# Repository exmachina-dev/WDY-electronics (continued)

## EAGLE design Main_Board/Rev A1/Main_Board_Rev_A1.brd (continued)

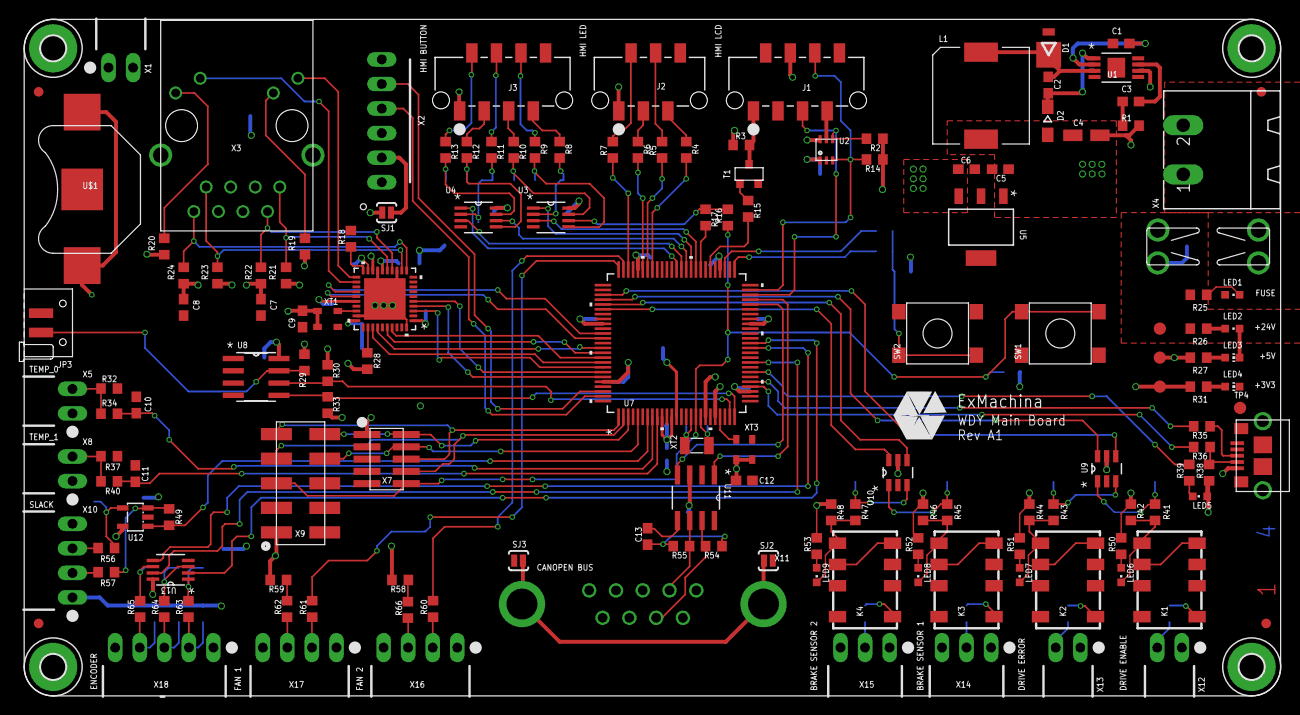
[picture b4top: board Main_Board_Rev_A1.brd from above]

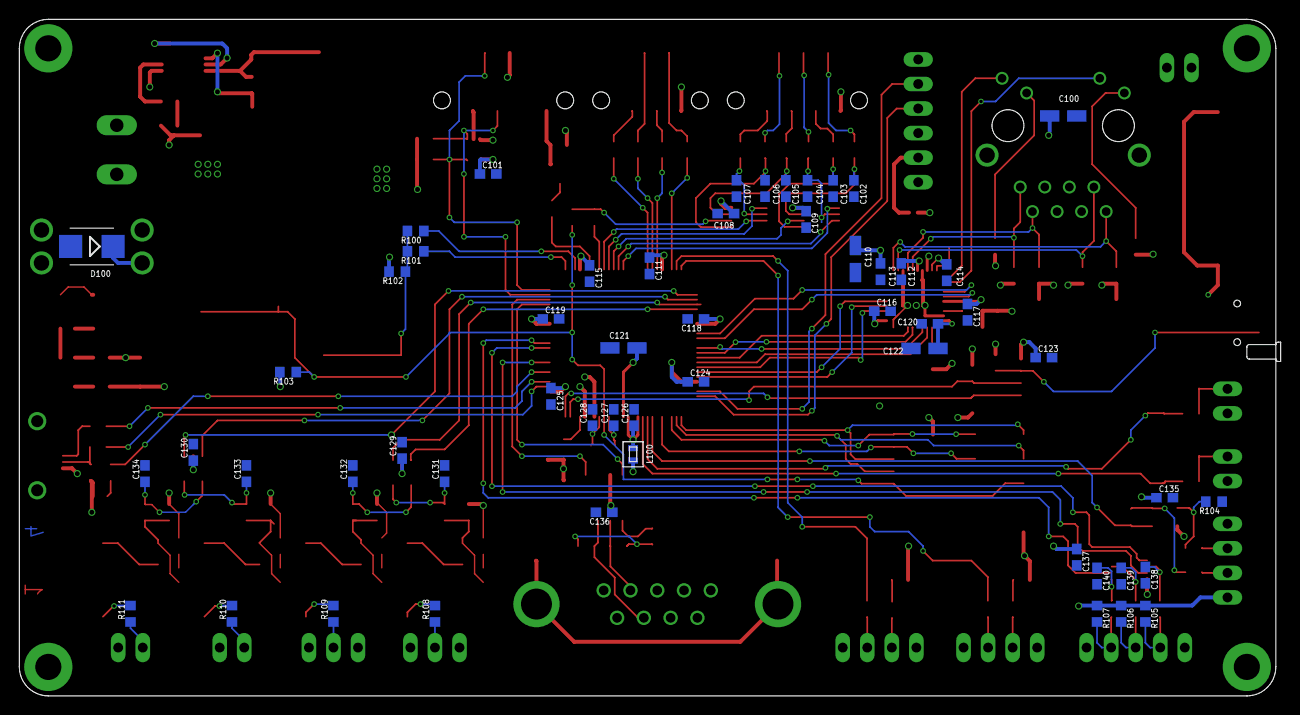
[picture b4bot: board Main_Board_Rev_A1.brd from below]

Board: 4 copper layers, 130.0 x 70.0 mm, 209 parts (55 on the bottom side), 154 nets.

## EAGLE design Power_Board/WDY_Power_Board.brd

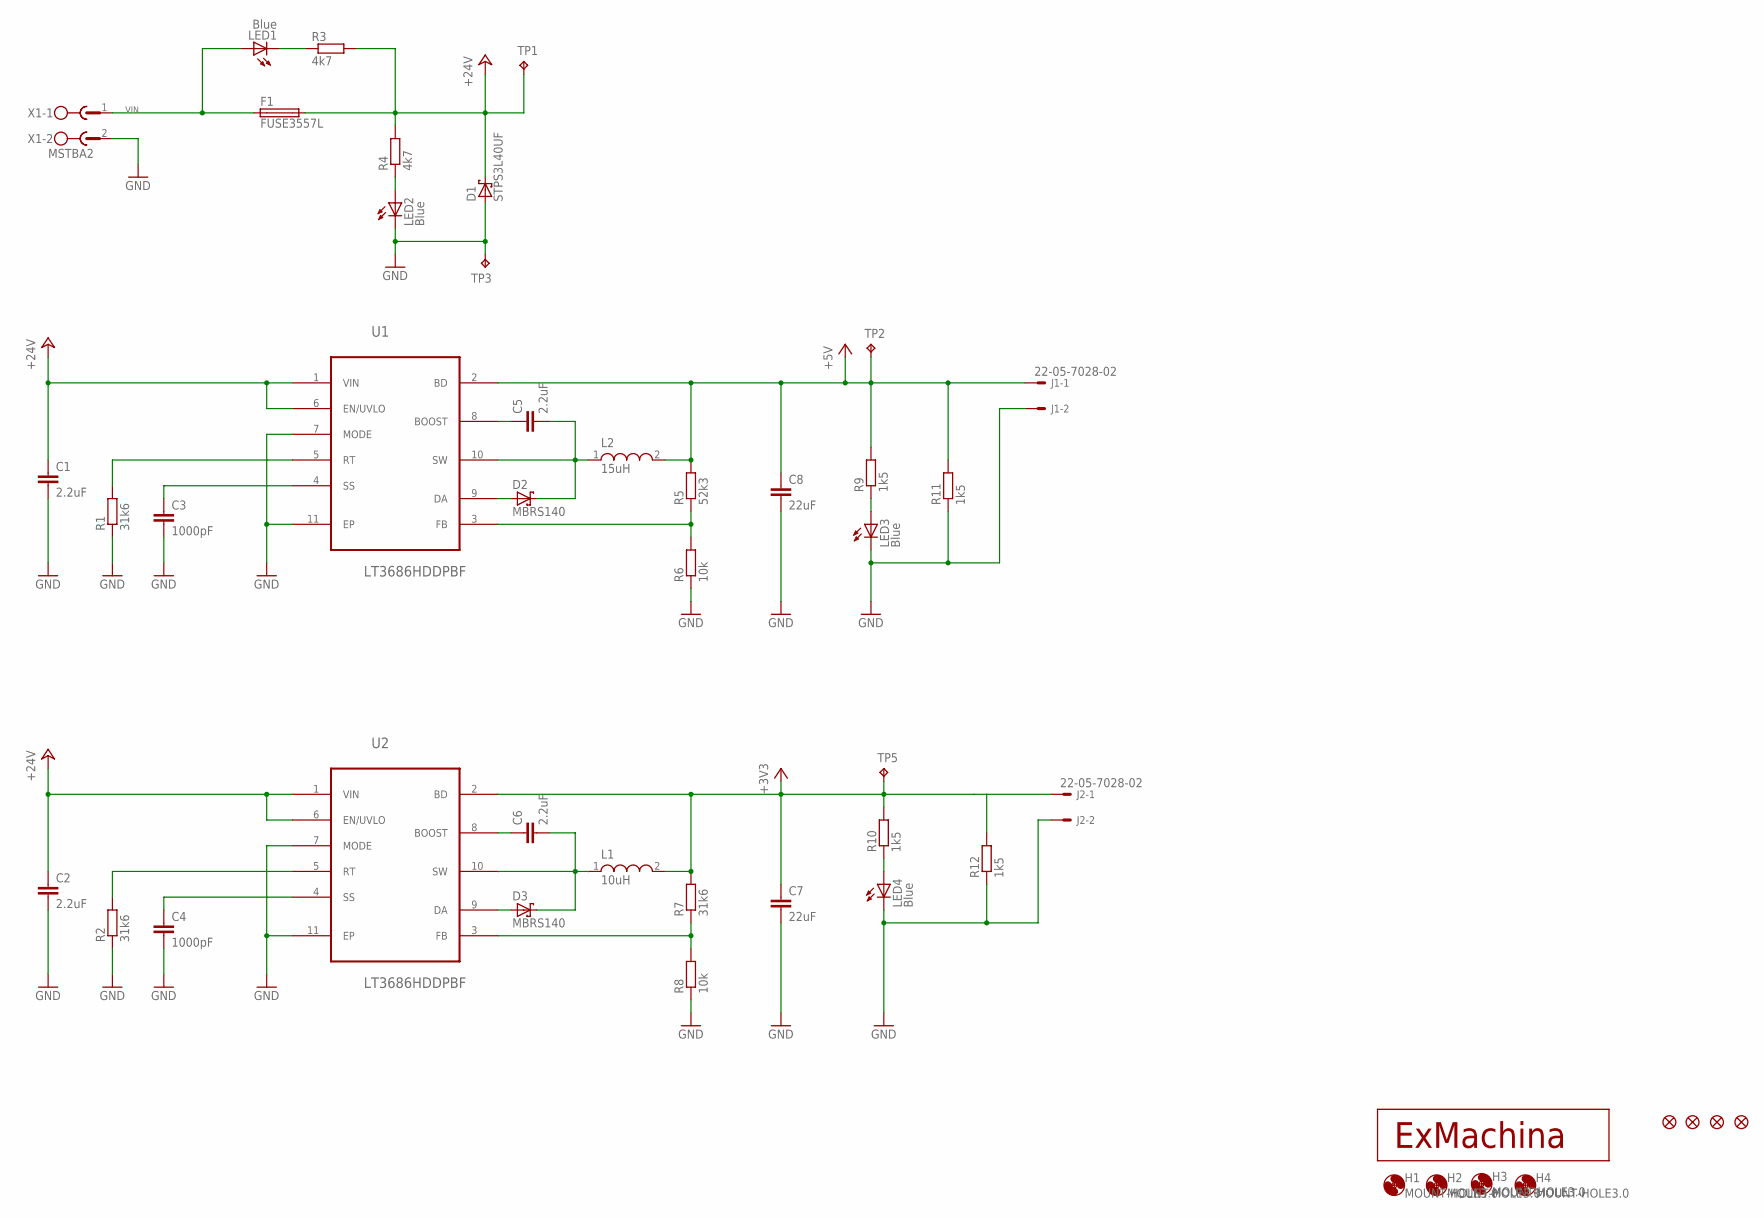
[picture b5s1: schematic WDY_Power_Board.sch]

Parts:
C1, C2, C5, C6: 2.2uF; C0603; MPN GRT188R61H225KE13D
C3, C4: 1000pF; C0603; MPN MC0603B102K500CT
C7, C8: 22uF; C0805; MPN MCMT21N220F250CT
D1: STPS3L40UF; SMB
D2, D3: MBRS140; DO-214AA; MPN MBRS140T3G
F1: FUSE3557L; 3557-LITTLE; MPN 3557
H1, H2, H3, H4: MOUNT-HOLE3.0; 3,0
J1, J2: 22-05-7028-02; 7395-02; MPN 22-05-7028
JP1, JP2, JP3, JP4: FIDUCIAL1X2; FIDUCIAL-1X2
L1: 10uH; WE-PD2_5848/5820; MPN 74477410
L2: 15uH; WE-PD2_5848/5820; MPN 744774115
LED1, LED2: Blue; CHIPLED_0603; MPN OVS-0603
LED3, LED4: Blue; CHIP-LED0603; MPN OVS-0604
R1, R2, R7: 31k6; R0603; MPN MC0063W060311K5
R3, R4: 4k7; R0603; MPN MCMR06X4701FTL
R5: 52k3; R0603; MPN MC0063W0603152K3
R6, R8: 10k; R0603; MPN MCMR06X1002FTL
R9, R10, R11, R12: 1k5; R0603; MPN MC0063W060311K5
TP1, TP2, TP3, TP5: TPB1,27; B1,27
U1, U2: LT3686HDDPBF; DFN300X300X80-11N
U$1: EXMACHINA-LOGO-NAME; EXM-LOGO-BASELINE
X1: MSTBA2

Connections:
+3V3: C7.1, J2.1, L1.2, R7.2, R10.2, R12.2, TP5.TP, U2.2 (BD)
+5V: C8.1, J1.1, L2.2, R5.2, R9.2, R11.2, TP2.TP, U1.2 (BD)
+24V: C1.1, C2.1, D1.C, F1.3 (2), F1.4 (2), R3.2, R4.2, TP1.TP, U1.1 (VIN), U1.6 (EN/UVLO), U2.1 (VIN), U2.6 (EN/UVLO)
GND: C1.2, C2.2, C3.2, C4.2, C7.2, C8.2, D1.A, J1.2, J2.2, LED2.C, LED3.C, LED4.C, R1.1, R2.1, R6.1, R8.1, R11.1, R12.1, TP3.TP, U1.7 (MODE), U1.11 (EP), U2.7 (MODE), U2.11 (EP), X1.2
unnamed: R1.2, U1.5 (RT)
unnamed: R7.1, R8.2, U2.3 (FB)
unnamed: C3.1, U1.4 (SS)
unnamed: R2.2, U2.5 (RT)
unnamed: C4.1, U2.4 (SS)
unnamed: R5.1, R6.2, U1.3 (FB)
unnamed: C6.1, U2.8 (BOOST)
unnamed: C5.1, U1.8 (BOOST)
unnamed: C5.2, D2.C, L2.1, U1.10 (SW)
unnamed: D2.A, U1.9 (DA)
unnamed: C6.2, D3.C, L1.1, U2.10 (SW)
unnamed: D3.A, U2.9 (DA)
unnamed: LED2.A, R4.1
unnamed: LED1.C, R3.1
unnamed: LED4.A, R10.1
unnamed: LED3.A, R9.1
VIN: F1.1, F1.2 (1), LED1.A, X1.1

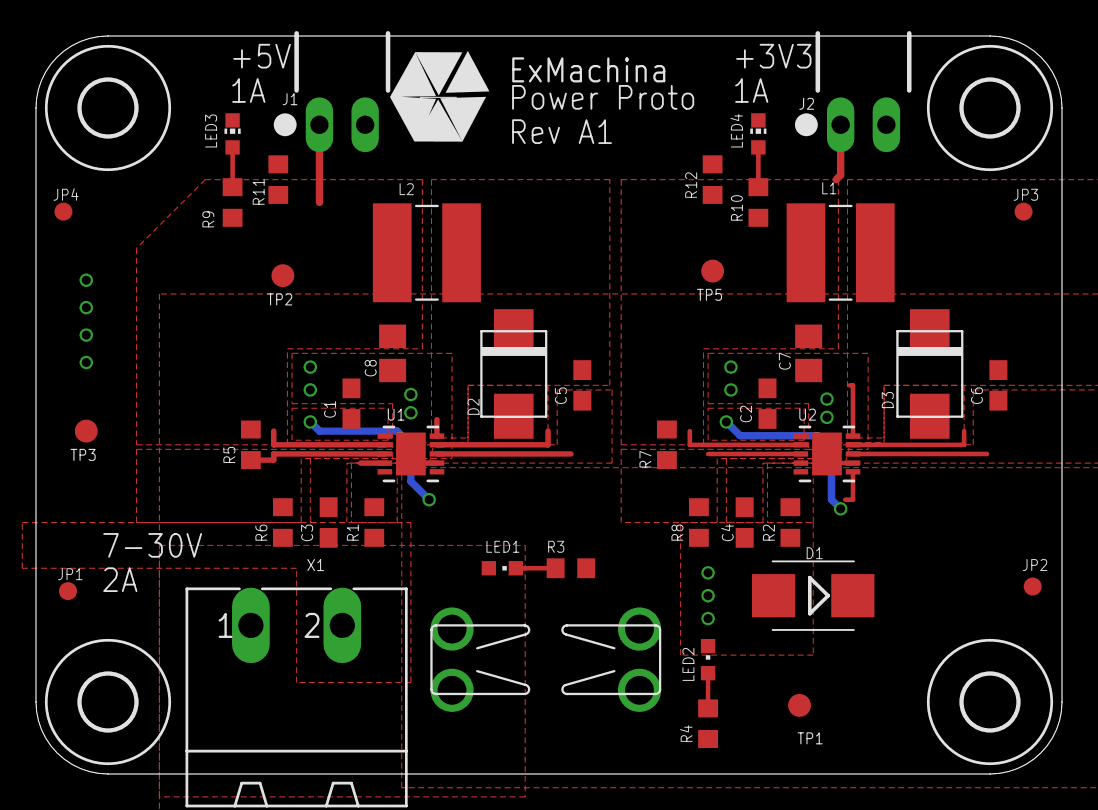
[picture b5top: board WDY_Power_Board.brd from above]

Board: 2 copper layers, 57.0 x 41.0 mm, 48 parts (0 on the bottom side), 21 nets.
